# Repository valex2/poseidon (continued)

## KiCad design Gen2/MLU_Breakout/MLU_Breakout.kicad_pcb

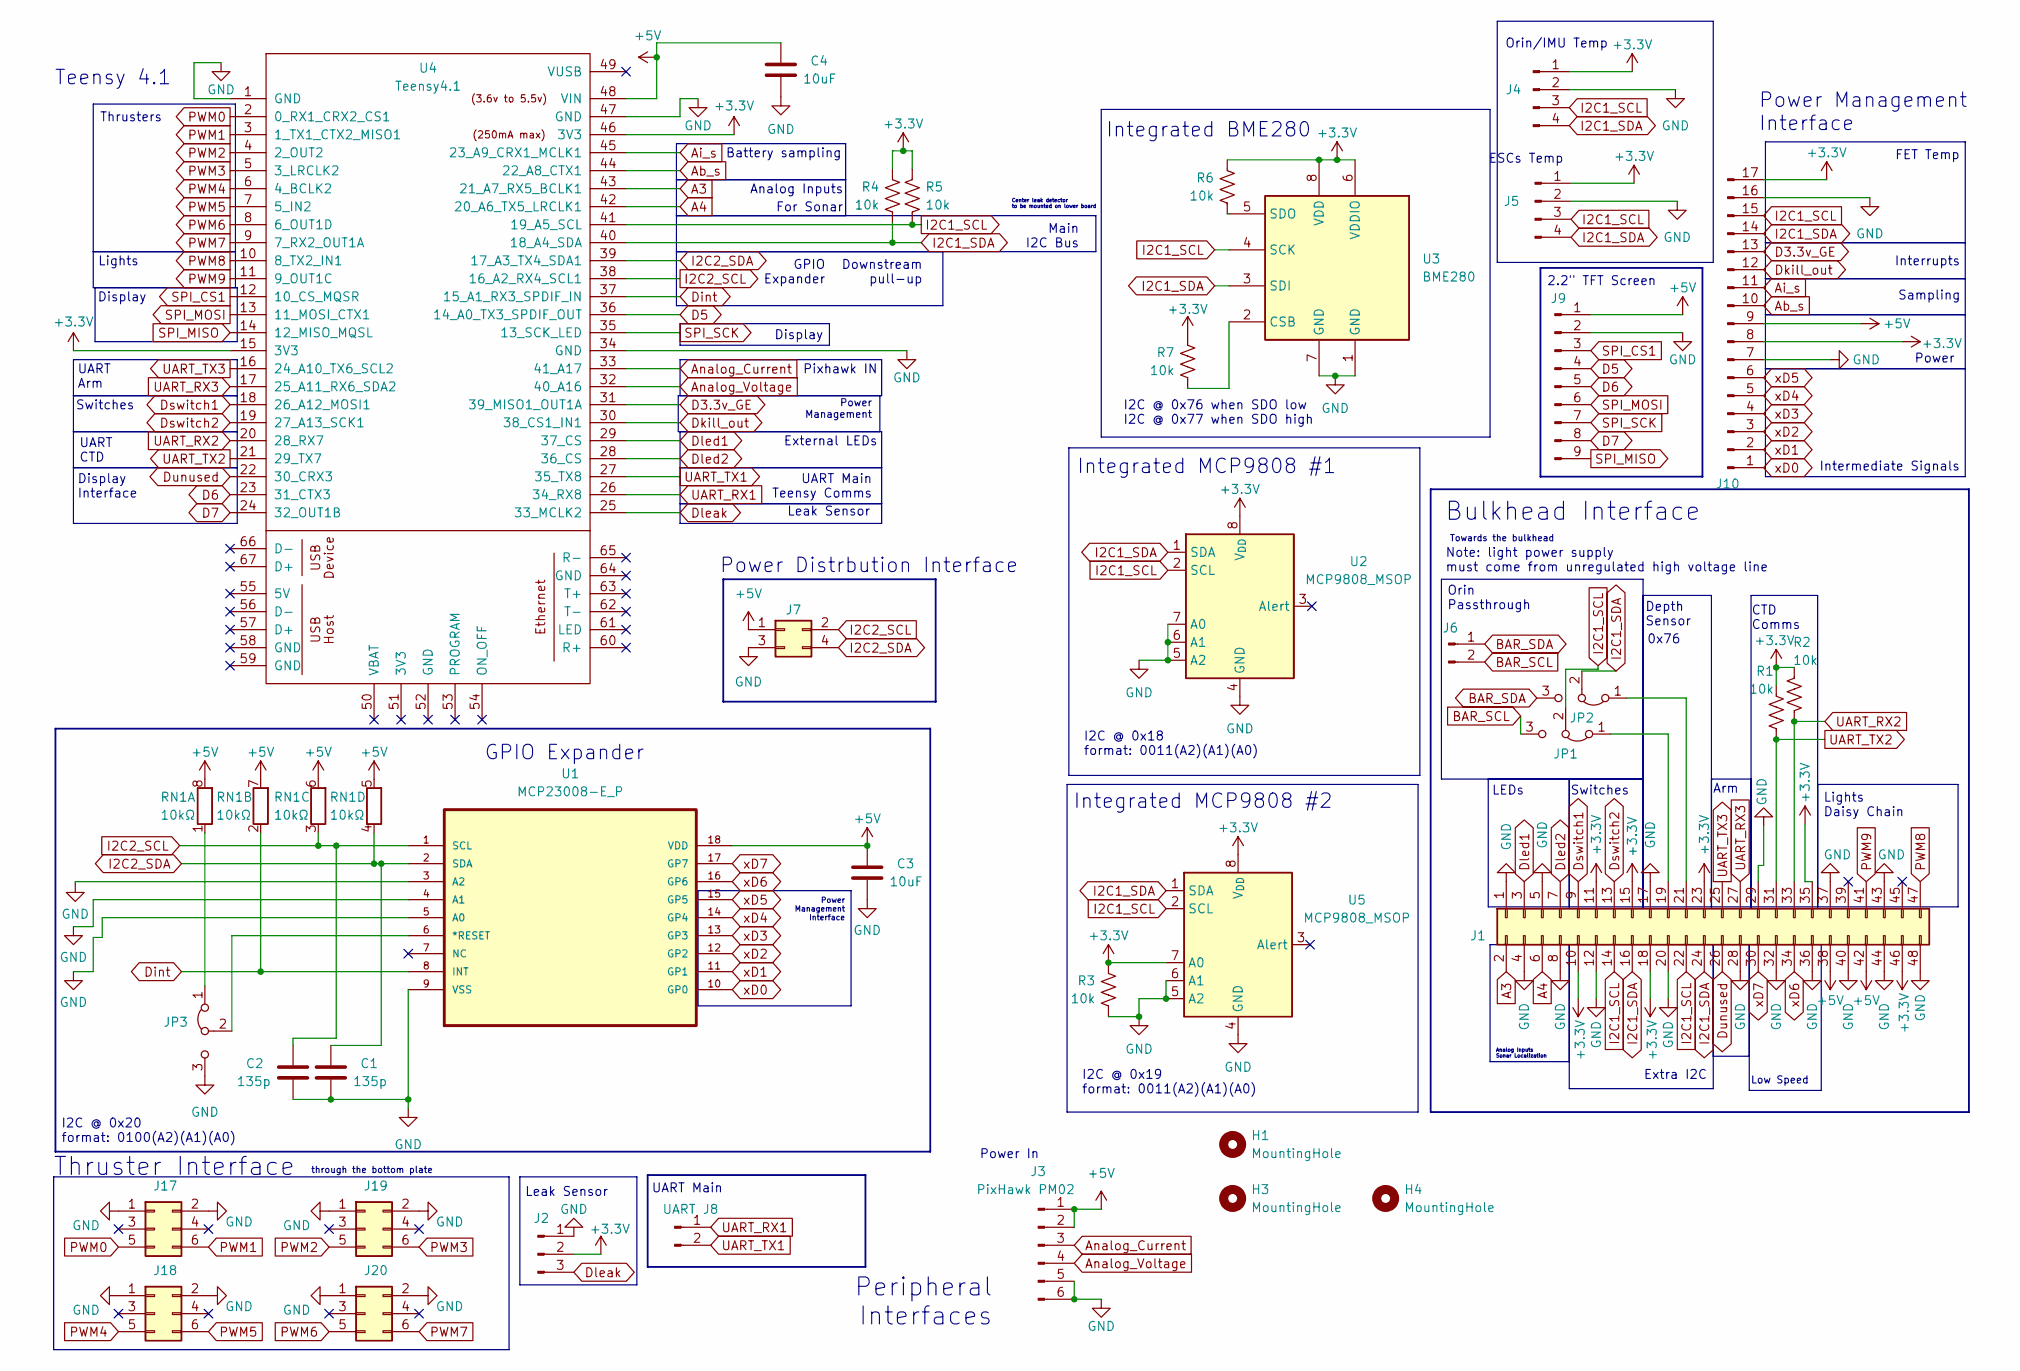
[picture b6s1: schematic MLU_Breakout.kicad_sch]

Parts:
C1, C2: 135p; C_0603_1608Metric_Pad1.08x0.95mm_HandSolder
C3, C4: 10uF; C_0805_2012Metric_Pad1.18x1.45mm_HandSolder
H1, H3, H4: MountingHole; MountingHole_3.2mm_M3
J1: Conn_02x24_Odd_Even; PinSocket_2x24_P2.54mm_Horizontal
J2: Conn_01x03_Pin; PinHeader_1x03_P2.54mm_Vertical
J3: PixHawk PM02; PinSocket_1x06_P2.54mm_Vertical
J4: BUS1; PinSocket_1x04_P2.54mm_Vertical
J5: BUS2; PinSocket_1x04_P2.54mm_Vertical
J6: Conn_01x02_Pin; PinHeader_1x02_P2.54mm_Vertical
J7: Conn_02x02_Odd_Even; PinHeader_2x02_P2.54mm_Vertical
J8: UART; PinSocket_1x02_P2.54mm_Vertical
J9: Conn_01x09_Pin; PinHeader_1x09_P2.54mm_Vertical
J10: Conn_01x17_Pin; PinHeader_1x17_P2.54mm_Horizontal
J17, J18, J19, J20: Conn_02x03_Odd_Even; PinHeader_2x03_P2.54mm_Vertical
JP1, JP2, JP3: Jumper_3_Bridged12; SolderJumper-3_P1.3mm_Bridged2Bar12_RoundedPad1.0x1.5mm
R1, R2, R3, R4, R5, R6, R7: 10k; R_0805_2012Metric_Pad1.20x1.40mm_HandSolder
RN1: 10kΩ; R_Array_Convex_4x0612; Mfr P/N CAY16-103J4LF
U1: MCP23008-E_P; MCP3008; MPN MCP23008-E/P
U2, U5: MCP9808_MSOP; MSOP-8_3x3mm_P0.65mm
U3: BME280
U4: Teensy4.1; Teensy41

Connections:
+3.3V: J1.10, J1.11, J1.15, J1.18, J1.23, J1.35, J1.46, J2.2, J4.1, J5.1, J10.8, J10.17, R1.1, R2.1, R3.1, R4.1, R5.1, R6.1, R7.1, U2.8 (V_{DD}), U3.6 (VDDIO), U3.8 (VDD), U4.15 (3V3), U4.46 (3V3), U5.7 (A0), U5.8 (V_{DD})
+5V: C3.1, C4.1, J1.38, J1.42, J3.1, J3.2, J7.1, J9.1, J10.9, RN1.5 (R4.2), RN1.6 (R3.2), RN1.7 (R2.2), RN1.8 (R1.2), U1.18 (VDD), U4.48 (VIN)
A3: J1.2, U4.43 (21_A7_RX5_BCLK1)
A4: J1.6, U4.42 (20_A6_TX5_LRCLK1)
Ab_s: J10.10, U4.44 (22_A8_CTX1)
Ai_s: J10.11, U4.45 (23_A9_CRX1_MCLK1)
Analog_Current: J3.3, U4.33 (41_A17)
Analog_Voltage: J3.4, U4.32 (40_A16)
BAR_SCL: J6.2, JP1.3 (B)
BAR_SDA: J6.1, JP2.3 (B)
D3.3v_GE: J10.13, U4.31 (39_MISO1_OUT1A)
D5: J9.4, U4.36 (14_A0_TX3_SPDIF_OUT)
D6: J9.5, U4.23 (31_CTX3)
D7: J9.8, U4.24 (32_OUT1B)
Dint: RN1.2 (R2.1), U1.8 (INT), U4.37 (15_A1_RX3_SPDIF_IN)
Dkill_out: J10.12, U4.30 (38_CS1_IN1)
Dleak: J2.3, U4.25 (33_MCLK2)
Dled1: J1.3, U4.29 (37_CS)
Dled2: J1.7, U4.28 (36_CS)
Dswitch1: J1.9, U4.18 (26_A12_MOSI1)
Dswitch2: J1.13, U4.19 (27_A13_SCK1)
Dunused: J1.26, U4.22 (30_CRX3)
GND: C1.2, C2.2, C3.2, C4.2, J1.1, J1.4, J1.5, J1.8, J1.12, J1.17, J1.20, J1.28, J1.29, J1.32, J1.36, J1.37, J1.40, J1.43, J1.44, J1.48, J2.1, J3.5, J3.6, J4.2, J5.2, J7.3, J9.2, J10.7, J10.16, J17.1, J17.2, J18.1, J18.2, J19.1, J19.2, J20.1, J20.2, JP3.3 (B), R3.2, U1.3 (A2), U1.4 (A1), U1.5 (A0), U1.9 (VSS), U2.4 (GND), U2.5 (A2), U2.6 (A1), U2.7 (A0), U3.1 (GND), U3.7 (GND), U4.1 (GND), U4.34 (GND), U4.47 (GND), U5.4 (GND), U5.5 (A2), U5.6 (A1)
I2C1_SCL: J1.14, J1.22, J4.3, J5.3, J10.15, JP1.2 (C), R5.2, U2.2 (SCL), U3.4 (SCK), U4.41 (19_A5_SCL), U5.2 (SCL)
I2C1_SDA: J1.16, J1.24, J4.4, J5.4, J10.14, JP2.2 (C), R4.2, U2.1 (SDA), U3.3 (SDI), U4.40 (18_A4_SDA), U5.1 (SDA)
I2C2_SCL: C2.1, J7.2, RN1.3 (R3.1), U1.1 (SCL), U4.38 (16_A2_RX4_SCL1)
I2C2_SDA: C1.1, J7.4, RN1.4 (R4.1), U1.2 (SDA), U4.39 (17_A3_TX4_SDA1)
unnamed: J1.19, JP1.1 (A)
unnamed: J1.21, JP2.1 (A)
unnamed: JP3.1 (A), RN1.1 (R1.1)
unnamed: JP3.2 (C), U1.6 (*RESET)
unnamed: R7.2, U3.2 (CSB)
unnamed: R6.2, U3.5 (SDO)
PWM0: J17.5, U4.2 (0_RX1_CRX2_CS1)
PWM1: J17.6, U4.3 (1_TX1_CTX2_MISO1)
PWM2: J19.5, U4.4 (2_OUT2)
PWM3: J19.6, U4.5 (3_LRCLK2)
PWM4: J18.5, U4.6 (4_BCLK2)
PWM5: J18.6, U4.7 (5_IN2)
PWM6: J20.5, U4.8 (6_OUT1D)
PWM7: J20.6, U4.9 (7_RX2_OUT1A)
PWM8: J1.47, U4.10 (8_TX2_IN1)
PWM9: J1.41, U4.11 (9_OUT1C)
SPI_CS1: J9.3, U4.12 (10_CS_MQSR)
SPI_MISO: J9.9, U4.14 (12_MISO_MQSL)
SPI_MOSI: J9.6, U4.13 (11_MOSI_CTX1)
SPI_SCK: J9.7, U4.35 (13_SCK_LED)
UART_RX1: J8.1, U4.26 (34_RX8)
UART_RX2: J1.33, R2.2, U4.20 (28_RX7)
UART_RX3: J1.27, U4.17 (25_A11_RX6_SDA2)
UART_TX1: J8.2, U4.27 (35_TX8)
UART_TX2: J1.31, R1.2, U4.21 (29_TX7)
UART_TX3: J1.25, U4.16 (24_A10_TX6_SCL2)
xD0: J10.1, U1.10 (GP0)
xD1: J10.2, U1.11 (GP1)
xD2: J10.3, U1.12 (GP2)
xD3: J10.4, U1.13 (GP3)
xD4: J10.5, U1.14 (GP4)
xD5: J10.6, U1.15 (GP5)
xD6: J1.34, U1.16 (GP6)
xD7: J1.30, U1.17 (GP7)

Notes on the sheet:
UART Main Teensy Comms
Switches
Display Interface
Power Management Interface
For Sonar
Teensy 4.1
Thrusters
Arm
Center leak detector to be mounted on lower board
ESCs Temp
Intermediate Signals
Battery sampling
Lights
Power Management
Lights Daisy Chain
Peripheral Interfaces
Power Distrbution Interface
Integrated BME280
Display
GPIO Expander
Extra I2C
Power
Note: light power supply must come from unregulated high voltage line
I2C @ 0x76 when SDO low I2C @ 0x77 when SDO high
Bulkhead Interface
Low Speed
Sampling
Leak Sensor
Pixhawk IN
Orin/IMU Temp
External LEDs
I2C @ 0x18 format: 0011(A2)(A1)(A0)
I2C @ 0x19 format: 0011(A2)(A1)(A0)
Power In
Thruster Interface
Analog Inputs Sonar Localization
Interrupts
Downstream pull-up
UART Main
CTD Comms

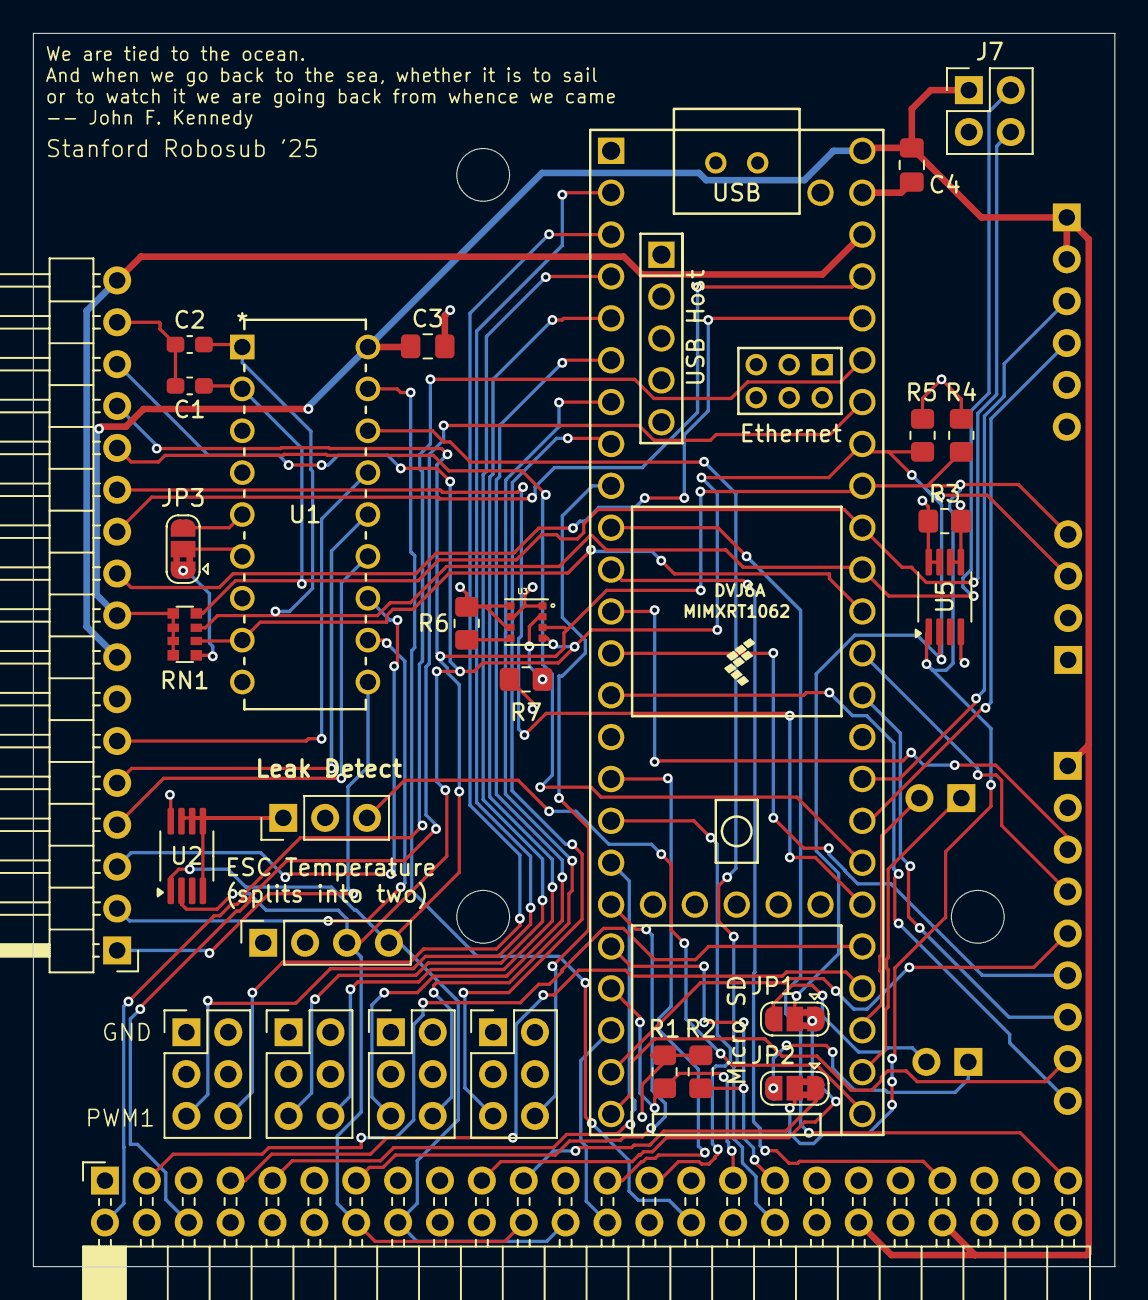
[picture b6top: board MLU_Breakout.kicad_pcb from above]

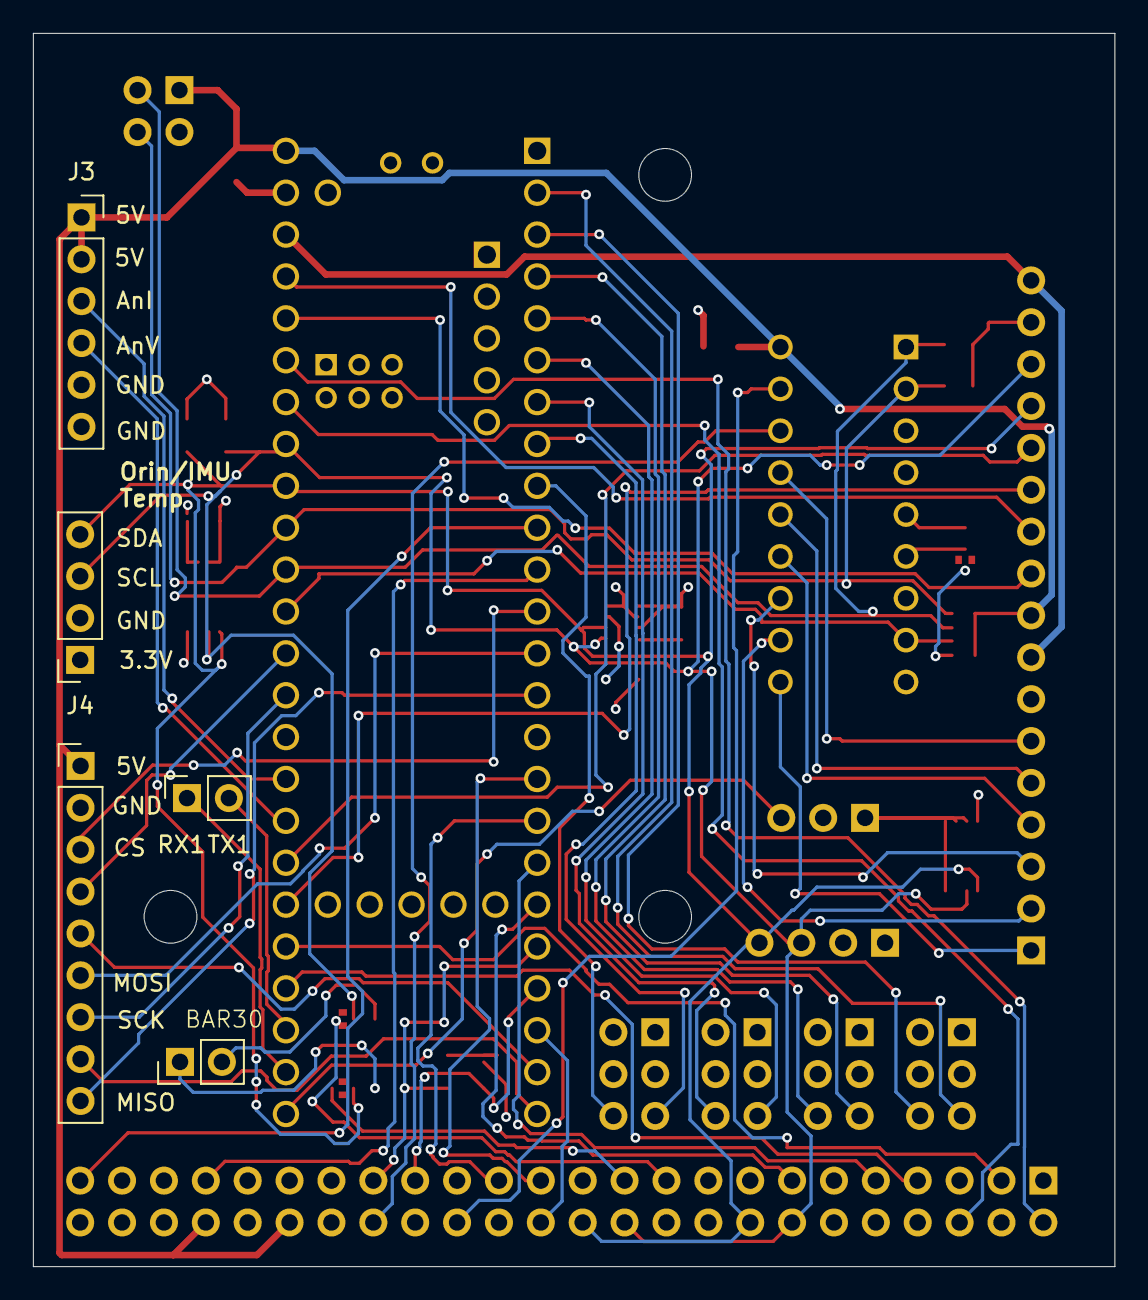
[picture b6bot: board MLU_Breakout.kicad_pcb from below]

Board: 4 copper layers, 65.6 x 74.8 mm, 37 parts (5 on the bottom side), 61 nets.

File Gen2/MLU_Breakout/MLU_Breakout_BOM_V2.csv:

Reference,Value,Qty,DNP,Supplier 1,Supplier 1 P/N,Supplier 1 S/N
"C1,C2",135p,2,,https://www.digikey.com/en/products/detail/murata-electronic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,,490-1427-1-ND
"C3,C4",10uF,2,,https://www.digikey.com/en/products/detail/murata-electronic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,,490-6473-1-ND
"J1,J2,J3,J4,J5,J6,J7,J8,J9,J10,J17,J18,J19,J20,U4",-- mixed values --,15,,,,
"R1,R2,R3,R4,R5,R6,R7",10k,7,,https://www.digikey.com/en/products/detail/panasonic-electro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,,P10KACT-ND
RN1,10kΩ,1,,https://www.digikey.com/en/products/detail/bourns-inc/CAY16-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,,CAY16-103J4LFCT-ND
U1,MCP23008-E_P,1,,https://www.digikey.com/en/products/detail/microchip-technol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,,MCP23008-E/P-ND
"U2,U5",MCP9808_MSOP,2,,https://www.digikey.com/en/products/detail/microchip-technol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,,MCP9808T-E/MSCT-ND
U3,BME280,1,,https://www.digikey.com/en/products/detail/bosch-sensortec/B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,,828-1063-1-ND

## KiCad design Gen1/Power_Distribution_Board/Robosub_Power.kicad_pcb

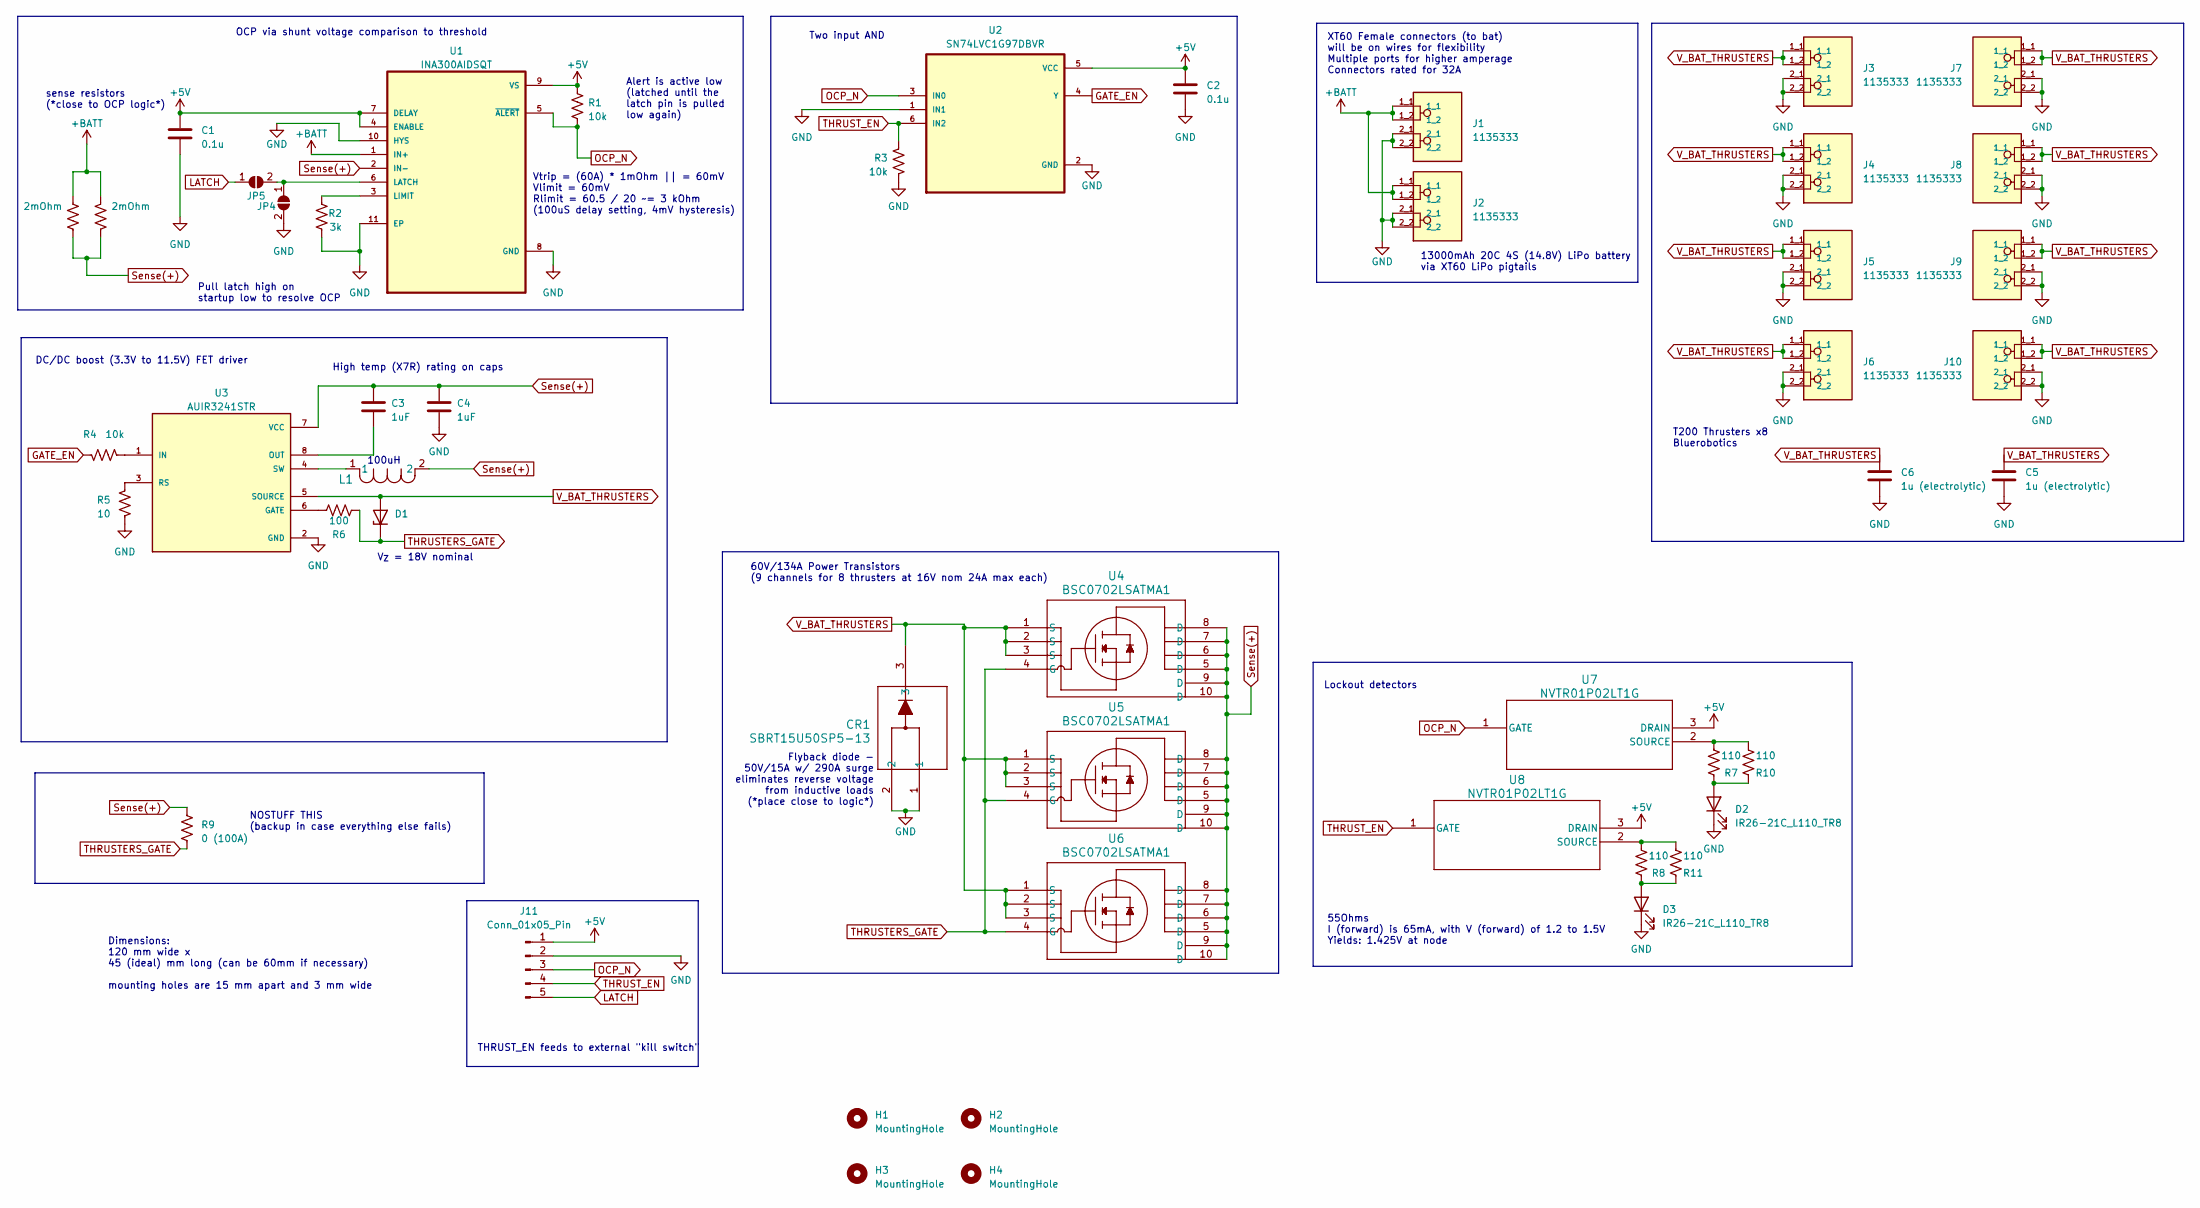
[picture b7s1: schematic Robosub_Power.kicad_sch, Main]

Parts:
C1, C2: 0.1u; C_0805_2012Metric_Pad1.18x1.45mm_HandSolder
C3, C4: 1uF; C_1812_4532Metric_Pad1.57x3.40mm_HandSolder
C5, C6: 1u (electrolytic); UCB1V0R1MCL1GS
CR1: SBRT15U50SP5-13; POWERDI5_DIO
D1: 1SMA5931BT3; D_SMA
D2, D3: IR26-21C_L110_TR8; LED_1206_3216Metric
H1, H2, H3, H4: MountingHole; MountingHole_3.2mm_M3
J1, J2, J3, J4, J5, J6, J7, J8, J9, J10: 1135333; PHOENIX_1135333
J11: Conn_01x05_Pin; PinHeader_1x05_P2.54mm_Vertical
JP4, JP5: SolderJumper_2_Open; SolderJumper-2_P1.3mm_Open_Pad1.0x1.5mm
L1: 74477420; IND_5848-WE-PD2_WRE
R1, R3, R4: 10k; R_0805_2012Metric_Pad1.20x1.40mm_HandSolder
R2: 3k; R_0805_2012Metric_Pad1.20x1.40mm_HandSolder
R5: 10; R_0805_2012Metric_Pad1.20x1.40mm_HandSolder
R6: 100; R_0805_2012Metric_Pad1.20x1.40mm_HandSolder
R7, R8, R10, R11: 110; R_0805_2012Metric_Pad1.20x1.40mm_HandSolder
R9: 0 (100A); R_2512_6332Metric_Pad1.40x3.35mm_HandSolder
U1: INA300AIDSQT; SON40P200X200X80-11N
U2: SN74LVC1G97DBVR; SOT95P280X145-6N
U3: AUIR3241STR; SOIC127P600X175-8N_AUIR3241STR
U4, U5, U6: BSC0702LSATMA1
U7, U8: NVTR01P02LT1G; SOT-23-3_1P4X3P040_ONS
WSLP59312L000FEA_1, WSLP59312L000FEA_2: 2mOhm; RES_WSLP5931_.002OHM_VIS

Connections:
+5V: C1.1, C2.1, J11.1, R1.1, U1.4 (ENABLE), U1.7 (DELAY), U1.9 (VS), U2.5 (VCC), U7.3 (DRAIN), U8.3 (DRAIN)
+BATT: J1.1_1, J1.1_2, J2.1_1, J2.1_2, U1.1 (IN+), WSLP59312L000FEA_1.2, WSLP59312L000FEA_2.2
GATE_EN: R4.1, U2.4 (Y)
GND: C1.2, C2.2, C4.2, C5.2, C6.2, CR1.1, CR1.2, D2.1 (K), D3.1 (K), J1.2_1, J1.2_2, J2.2_1, J2.2_2, J3.2_1, J3.2_2, J4.2_1, J4.2_2, J5.2_1, J5.2_2, J6.2_1, J6.2_2, J7.2_1, J7.2_2, J8.2_1, J8.2_2, J9.2_1, J9.2_2, J10.2_1, J10.2_2, J11.2, JP4.2 (B), R2.2, R3.2, R5.2, U1.8 (GND), U1.10 (HYS), U1.11 (EP), U2.1 (IN1), U2.2 (GND), U3.2 (GND)
LATCH: J11.5, JP5.1 (A)
unnamed: D2.2 (A), R7.1, R10.1
unnamed: D3.2 (A), R8.1, R11.1
unnamed: JP4.1 (A), JP5.2 (B), U1.6 (LATCH)
unnamed: R2.1, U1.3 (LIMIT)
unnamed: R6.1, U3.6 (GATE)
unnamed: R4.2, U3.1 (IN)
unnamed: C3.2, U3.8 (OUT)
unnamed: R5.1, U3.3 (RS)
unnamed: L1.1, U3.4 (SW)
unnamed: R7.2, R10.2, U7.2 (SOURCE)
unnamed: R8.2, R11.2, U8.2 (SOURCE)
OCP_N: J11.3, R1.2, U1.5 (~ALERT), U2.3 (IN0), U7.1 (GATE)
Sense(+): C3.1, C4.1, L1.2, R9.1, U1.2 (IN-), U3.7 (VCC), U4.5 (D), U4.6 (D), U4.7 (D), U4.8 (D), U4.9 (D), U4.10 (D), U5.5 (D), U5.6 (D), U5.7 (D), U5.8 (D), U5.9 (D), U5.10 (D), U6.5 (D), U6.6 (D), U6.7 (D), U6.8 (D), U6.9 (D), U6.10 (D), WSLP59312L000FEA_1.1, WSLP59312L000FEA_2.1
THRUSTERS_GATE: D1.1 (K), R6.2, R9.2, U4.4 (G), U5.4 (G), U6.4 (G)
THRUST_EN: J11.4, R3.1, U2.6 (IN2), U8.1 (GATE)
V_BAT_THRUSTERS: C5.1, C6.1, CR1.3, D1.2 (A), J3.1_1, J3.1_2, J4.1_1, J4.1_2, J5.1_1, J5.1_2, J6.1_1, J6.1_2, J7.1_1, J7.1_2, J8.1_1, J8.1_2, J9.1_1, J9.1_2, J10.1_1, J10.1_2, U3.5 (SOURCE), U4.1 (S), U4.2 (S), U4.3 (S), U5.1 (S), U5.2 (S), U5.3 (S), U6.1 (S), U6.2 (S), U6.3 (S)

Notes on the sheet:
THRUST_EN feeds to external "kill switch"
Two input AND
Lockout detectors
Dimensions: 120 mm wide x 45 (ideal) mm long (can be 60mm if necessary) mounting holes are 15 mm apart and 3 mm wide
High temp (X7R) rating on caps
13000mAh 20C 4S (14.8V) LiPo battery via XT60 LiPo pigtails
Vtrip = (60A) * 1mOhm || = 60mV Vlimit = 60mV Rlimit = 60.5 / 20 ~= 3 kOhm (100uS delay setting, 4mV hysteresis)
Alert is active low (latched until the latch pin is pulled low again)
DC/DC boost (3.3V to 11.5V) FET driver
55Ohms I (forward) is 65mA, with V (forward) of 1.2 to 1.5V Yields: 1.425V at node
XT60 Female connectors (to bat) will be on wires for flexibility Multiple ports for higher amperage Connectors rated for 32A
Flyback diode - 50V/15A w/ 290A surge eliminates reverse voltage from inductive loads (*place close to logic*)
60V/134A Power Transistors (9 channels for 8 thrusters at 16V nom 24A max each)
V_{Z} = 18V nominal
100uH
NOSTUFF THIS (backup in case everything else fails)
T200 Thrusters x8 Bluerobotics
OCP via shunt voltage comparison to threshold
Pull latch high on startup low to resolve OCP
sense resistors (*close to OCP logic*)

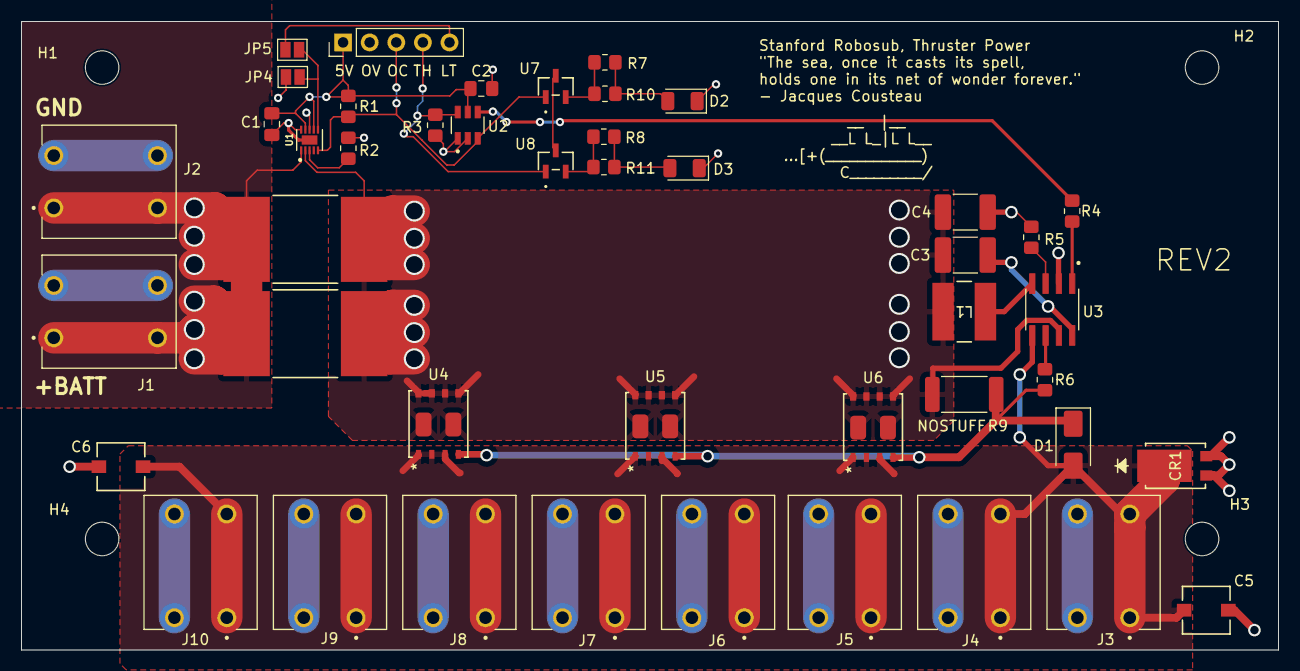
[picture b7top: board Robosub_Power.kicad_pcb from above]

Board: 2 copper layers, 120.0 x 60.0 mm, 49 parts (0 on the bottom side), 21 nets.

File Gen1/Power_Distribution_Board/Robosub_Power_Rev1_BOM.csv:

#,Reference,Qty,Value,Footprint,DNP,Supplier 1,Supplier 1 S/N,MFR,MFR S/N
1,"C1, C2",4,0.1u,Capacitor_SMD:C_0805_2012Metric_Pad1.18x1.45mm_HandSolder,,https://www.digikey.com/en/products/detail/yageo/CC0805KRX7R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,311-1140-1-ND,YAGEO,CC0805KRX7R9BB104
2,"C3, C4",4,1uF,Capacitor_SMD:C_1812_4532Metric_Pad1.57x3.40mm_HandSolder,,https://www.digikey.com/en/products/detail/knowles-syfer/181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,1608-1812Y2000105KSTWS2CT-ND,Knowles Syfer,1812Y2000105KSTWS2
3,"C5, C6",4,1u (electrolytic),Robosub Lib:UCB1V0R1MCL1GS,,https://www.digikey.com/en/products/detail/nichicon/UCB1V0R1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,493-9956-1-ND,Nichicon,UCB1V0R1MCL1GS
4,CR1,2,SBRT15U50SP5-13,SBRT15U50SP5_13:POWERDI5_DIO,,https://www.digikey.com/en/products/detail/diodes-incorporat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,SBRT15U50SP5-13DICT-ND,Diodes Incorporated,SBRT15U50SP5-13
5,D1,2,1SMA5931BT3,Diode_SMD:D_SMA,,https://www.digikey.com/en/products/detail/onsemi/SZ1SMA5931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,SZ1SMA5931BT3GOSCT-ND,onsemi,SZ1SMA5931BT3G
6,"D2, D3",4,IR26-21C_L110_TR8,LED_SMD:LED_1206_3216Metric,,https://www.digikey.com/en/products/detail/everlight-electro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,1080-1357-1-ND,Everlight Electronics Co Ltd,IR26-21C/L110/TR8
7,"H1, H2, H3, H4",8,MountingHole,MountingHole:MountingHole_3.2mm_M3,,,,,
8,"J1, J2, J3, J4, J5, J6, J7, J8, J9, J10",14,1135333,1135333_1:PHOENIX_1135333,,https://www.digikey.com/en/products/detail/phoenix-contact/1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,277-1135333CT-ND,Pheonix Contact,"SPT-THR 2,5/ 2-V-5,0 P20 R32"
9,J14,2,Conn_01x04,Connector_PinHeader_2.54mm:PinHeader_1x04_P2.54mm_Vertical,,,,,
10,"JP4, JP5",4,SolderJumper_2_Open,Jumper:SolderJumper-2_P1.3mm_Open_Pad1.0x1.5mm,,,,,
11,L1,2,74477420,Robosub Lib:IND_5848-WE-PD2_WRE,,https://www.digikey.com/en/products/detail/würth-elektronik/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,732-1278-1-ND,Würth Elektronik,74477420
12,"R1, R3, R4",6,10k,Resistor_SMD:R_0805_2012Metric_Pad1.20x1.40mm_HandSolder,,https://www.digikey.com/en/products/detail/yageo/RC0805FR-07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,311-10.0KCRCT-ND,YAGEO,RC0805FR-0710KL
13,R2,2,3k,Resistor_SMD:R_0805_2012Metric_Pad1.20x1.40mm_HandSolder,,https://www.digikey.com/en/products/detail/te-connectivity-p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,A126368CT-ND,TE Connectivity Passive Product,CRG0805F3K0
14,R5,2,10,Resistor_SMD:R_0805_2012Metric_Pad1.20x1.40mm_HandSolder,,https://www.digikey.com/en/products/detail/yageo/RC0805FR-07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,311-10.0CRCT-ND,YAGEO,RC0805FR-0710RL
15,"R6, R7, R8",6,100,Resistor_SMD:R_0805_2012Metric_Pad1.20x1.40mm_HandSolder,,https://www.digikey.com/en/products/detail/yageo/RC0805FR-07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,311-100CRCT-ND,YAGEO,RC0805FR-07100RL
16,R9,2,0 (100A),Resistor_SMD:R_2512_6332Metric_Pad1.40x3.35mm_HandSolder,,https://www.digikey.com/en/products/detail/bourns-inc./CSS2H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,118-CSS2H-2512C-000ECT-ND,Bourns Inc.,CSS2H-2512C-000E
17,U1,2,INA300AIDSQT,Robosub Lib:SON40P200X200X80-11N,,https://www.digikey.com/en/products/detail/texas-instruments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,296-37474-1-ND,Texas Instruments,INA300AIDSQT
18,U2,2,SN74LVC1G97DBVR,Robosub Lib:SOT95P280X145-6N,,https://www.digikey.com/en/products/detail/texas-instruments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,296-15581-1-ND,Texas Instruments,SN74LVC1G97DBVR
19,U3,2,AUIR3241STR,Robosub Lib:SOIC127P600X175-8N_AUIR3241STR,,https://www.digikey.com/en/products/detail/infineon-technolo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,AUIR3241SCT-ND,Infineon Technologies,AUIR3241STR
20,"U4, U5, U6",6,BSC0702LSATMA1,Robosub Lib:BSC0702LSATMA1,,https://www.digikey.com/en/products/detail/infineon-technolo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,448-BSC0702LSATMA1CT-ND,Infineon Technologies,BSC0702LSATMA1
21,"U7, U8",3,NVTR01P02LT1G,Robosub Lib:SOT-23-3_1P4X3P040_ONS,,https://www.digikey.com/en/products/detail/onsemi/NVTR01P02L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,NVTR01P02LT1GOSCT-ND,onsemi,NVTR01P02LT1G
22,"WSLP59312L000FEA_1, WSLP59312L000FEA_2",4,2mOhm,WSLP59312L000FEA:RES_WSLP5931_.002OHM_VIS,,https://www.digikey.com/en/products/detail/vishay-dale/WSLP5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,541-10013-1-ND,Vishay Dale,WSLP59312L000FEA
23,Hall effect,1,,,,https://www.digikey.com/en/products/detail/littelfuse-inc/55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,55140-3H-02-A-ND,Littelfuse Inc.,55140-3H-02-A
24,Magnet,1,,,,https://www.digikey.com/en/products/detail/littelfuse-inc/H-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,F12127-ND,Littelfuse Inc.,H-58-MAGNET

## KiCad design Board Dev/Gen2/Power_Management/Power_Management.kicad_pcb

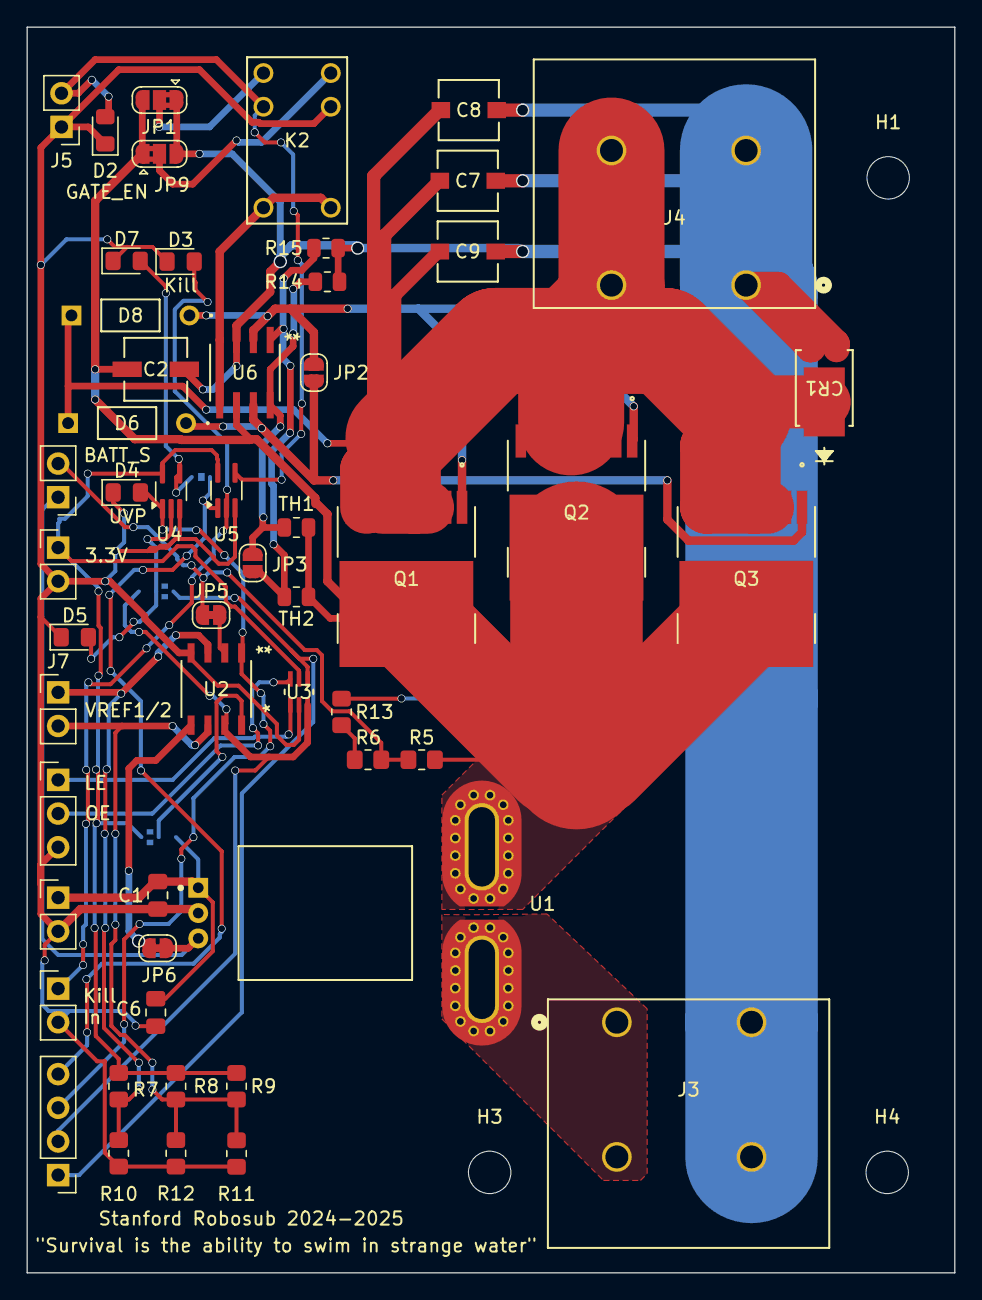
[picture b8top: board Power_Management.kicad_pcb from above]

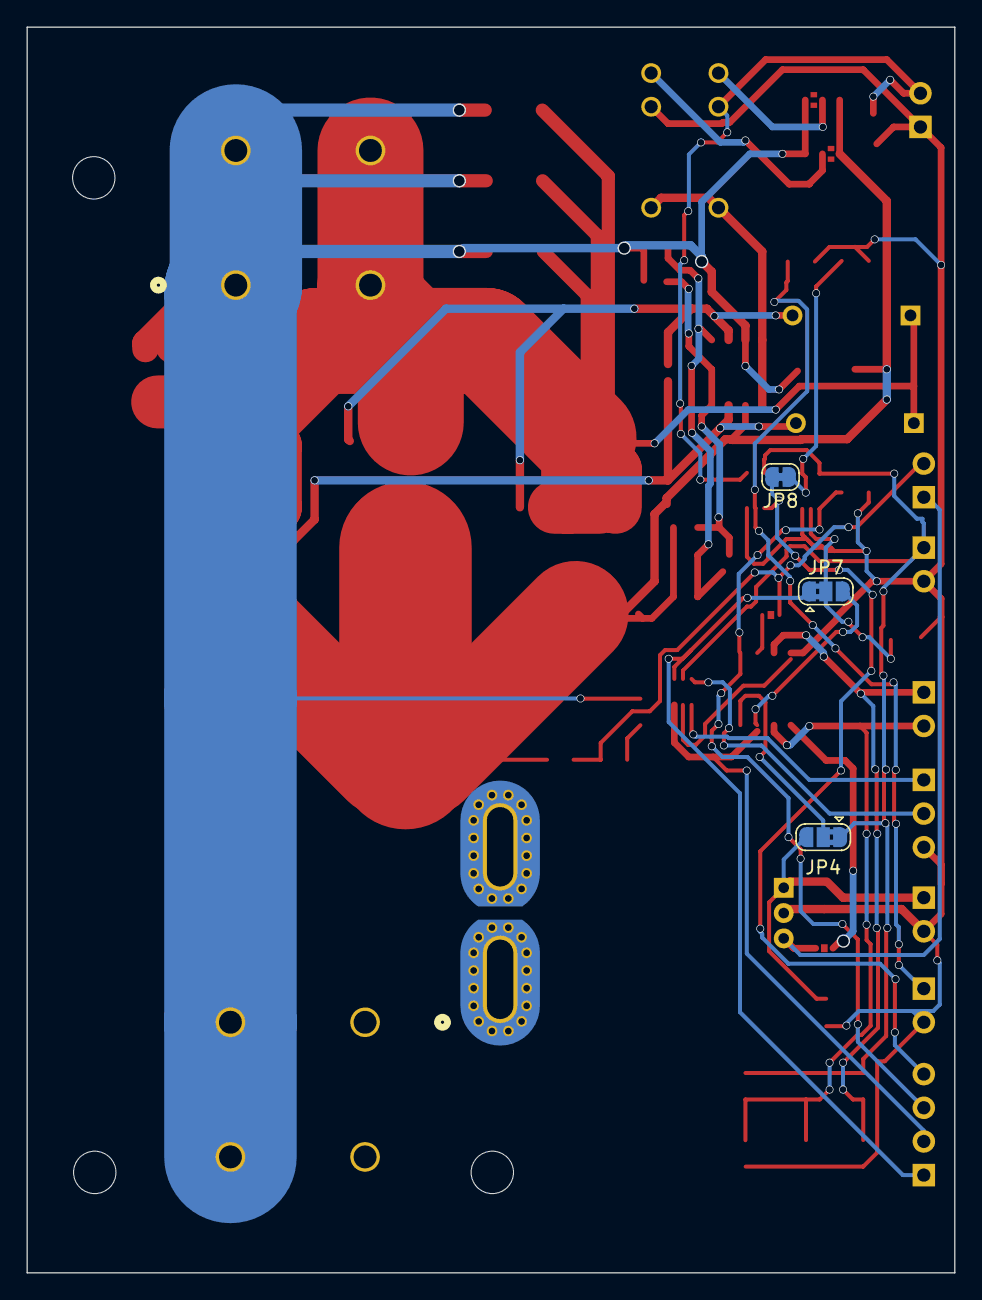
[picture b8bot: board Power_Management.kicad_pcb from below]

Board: 2 copper layers, 70.0 x 94.0 mm, 59 parts (3 on the bottom side), 32 nets.

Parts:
C1: 0.1u; C_0805_2012Metric_Pad1.18x1.45mm_HandSolder
C2: 10uF; CAP_EEE-1CA100SR_PAN
C6: 10uF; C_0805_2012Metric_Pad1.18x1.45mm_HandSolder
C7, C8, C9: 1u; U2-D_NCH
CR1: SBRT15U50SP5-13; POWERDI5_DIO
D2, D3, D4, D5, D7: LED; LED_0805_2012Metric_Pad1.15x1.40mm_HandSolder
D6, D8: D_Zener; 1N5242B
H1, H3, H4: MountingHole; MountingHole_3.2mm_M3
J1, J2, J5, J6, J7, J10: Conn_01x02_Pin; PinHeader_1x02_P2.54mm_Vertical
J3, J4: 1986660-2; CONN2_1986660-2_TEC
J8: Conn_01x04_Pin; PinHeader_1x04_P2.54mm_Vertical
J9: Conn_01x03_Pin; PinHeader_1x03_P2.54mm_Vertical
JP1, JP4, JP7, JP9: SolderJumper_3_Bridged12; SolderJumper-3_P1.3mm_Bridged2Bar12_RoundedPad1.0x1.5mm
JP2, JP3: SolderJumper_2_Open; SolderJumper-2_P1.3mm_Open_RoundedPad1.0x1.5mm
JP5, JP6, JP8: SolderJumper_2_Bridged; SolderJumper-2_P1.3mm_Bridged_RoundedPad1.0x1.5mm
K2: G5V-1 DC3; RELAY_G5V-1_OMR
Q1, Q2, Q3: MCTL160N15Y-TP; TOLL-8L_MCC
R5, R6: 100k; R_0805_2012Metric_Pad1.20x1.40mm_HandSolder
R7: 150k; R_0805_2012Metric_Pad1.20x1.40mm_HandSolder
R8, R9, R11, R12: R_0805_2012Metric_Pad1.20x1.40mm_HandSolder
R10: 200k; R_0805_2012Metric_Pad1.20x1.40mm_HandSolder
R13: 500k; R_0805_2012Metric_Pad1.20x1.40mm_HandSolder
R14, R15: 100k; R_0805_2012Metric
TH1, TH2: Thermistor_US; R_0805_2012Metric
U1: ACS758ECB-200U-PFF-T; Allegro_MicroSystems,_LLC-CB-5-PFF-0-0-MFG
U2: LM393DT
U3: SN74LVC1G373DCKR; SN74LVC
U4, U5: 74LVC1G08; SOT-353_SC-70-5_Handsoldering
U6: LTC1255CS8-PBF; LTC1255

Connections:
+3.3V: J6.1, JP4.1 (A), R7.1, R8.1, R9.1, U3.5 (VCC), U4.5 (VCC), U5.5 (VCC)
+5V: C1.2, C6.1, J2.1, JP4.3 (B), U1.1 (VCC)
/Battery_input/+BATT_HALL: J3.1A, J3.1B, U1.4 (IP+)
/Battery_input/-Batt: C2.2, C7.2, C8.2, C9.2, CR1.1, CR1.2, J3.2A, J3.2B, J4.1A, J4.1B, JP1.1 (A), JP9.3 (B), R13.2, R14.1, R15.1, U6.3 (GND)
/FET_control_logic/3.3V_GATE_EN: D2.2 (A), J5.2, K2.2, U5.4
/FET_control_logic/Kill_Switch: D3.2 (A), J10.1, U5.2
/FET_control_logic/OCP_COMP: J8.2, JP7.3 (B), U2.7 (OUT2), U3.3 (D)
/FET_control_logic/OCP_LATCH: J8.1, JP7.1 (A), U3.4 (Q)
/FET_control_logic/UVP_COMP: D4.2 (A), J8.3, U2.1 (OUT1), U4.1
/FETs/+Batt: C2.1, JP1.3 (B), JP9.1 (A), Q1.9 (D), Q2.9 (D), Q3.9 (D), R5.1, TH1.1, TH2.1, U1.5 (IP-), U6.6 (VS)
/FETs/GATE1_DRIVE: D8.1 (K), JP2.1 (A), Q1.1 (G), Q2.1 (G), U6.2 (GATE1)
/FETs/GATE2_DRIVE: D6.1 (K), JP2.2 (B), Q3.1 (G), U6.7 (GATE2)
/FETs/V_THRUST: C7.1, C8.1, C9.1, CR1.3, D6.2 (A), D8.2 (A), J4.2A, J4.2B, Q1.2 (S), Q1.3 (S), Q1.4 (S), Q1.5 (S), Q1.6 (S), Q1.7 (S), Q1.8 (S), Q2.2 (S), Q2.3 (S), Q2.4 (S), Q2.5 (S), Q2.6 (S), Q2.7 (S), Q2.8 (S), Q3.2 (S), Q3.3 (S), Q3.4 (S), Q3.5 (S), Q3.6 (S), Q3.7 (S), Q3.8 (S)
/OCP_UVP_detect/BATT_SAMPLE: J1.2, JP5.1 (A), R5.2, R6.1
/OCP_UVP_detect/ISENSE_ANALOG: J1.1, JP6.2 (B), U1.3 (VIOUT)
/OCP_UVP_detect/LE_Teensy: J9.1, U3.1 (LE)
/OCP_UVP_detect/OE_Teensy: J9.2, U3.6 (*OE)
GATE_DRIVER_EN: K2.5, K2.6, U6.4 (IN1), U6.5 (IN2)
GND: C1.1, C6.2, D2.1 (K), D3.1 (K), D4.1 (K), D5.1 (K), D7.1 (K), J2.2, J5.1, J6.2, J9.3, J10.2, K2.9, R10.2, R11.2, R12.2, U1.2 (GND), U2.4 (VCC-), U3.2 (GND), U4.3 (GND), U5.3 (GND)
unnamed: D5.2 (A), JP7.2 (C), U4.2
unnamed: D7.2 (A), JP8.1 (A), U4.4
unnamed: J8.4, JP8.2 (B), U5.1
unnamed: JP1.2 (C), K2.1
unnamed: JP3.1 (A), R15.2, TH2.2, U6.1 (DS1)
unnamed: JP3.2 (B), R14.2, TH1.2, U6.8 (DS2)
unnamed: JP4.2 (C), U2.8 (VCC+)
unnamed: JP5.2 (B), U2.2 (IN1-)
unnamed: JP6.1 (A), U2.5 (IN2+)
unnamed: JP9.2 (C), K2.10
unnamed: R6.2, R13.1
VREF1: J7.1, R7.2, R10.1, U2.3 (IN1+)
VREF2: J7.2, R8.2, R9.2, R11.1, R12.1, U2.6 (IN2-)

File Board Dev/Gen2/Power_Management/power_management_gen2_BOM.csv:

Reference,Value,Qty,Supplier 1,Supplier 1 S/N,,Qty (excess)
C1,0.1u,1,https://www.digikey.com/en/products/detail/samsung-electro-m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,1276-1003-1-ND,,3
C2,10uF,1,https://www.digikey.com/en/products/detail/panasonic-electro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,PCE3878CT-ND,,3
C6,10uF,1,https://www.digikey.com/en/products/detail/samsung-electro-m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,1276-1096-1-ND,,3
"C7,C8,C9",1u,3,https://www.digikey.com/en/products/detail/nichicon/UCB1V0R1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,493-9956-1-ND,,5
CR1,SBRT15U50SP5-13,1,https://www.digikey.com/en/products/detail/diodes-incorporat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,SBRT15U50SP5-13DICT-ND,,3
"D2,D3,D4,D5,D7",LED,5,https://www.digikey.com/en/products/detail/w%C3%BCrth-elektr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,732-4982-1-ND,,7
"D6,D8",D_Zener,2,https://www.digikey.com/en/products/detail/onsemi/1N5242B/977596,1N5242B-ND,,4
"H1,H3,H4,J1,J2,J5,J6,J7,J8,J9,J10,R8,R9,R11,R12",-- mixed values --,15,,,,17
"J3,J4",1986660-2,2,https://www.digikey.com/en/products/detail/te-connectivity-a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,A107722-ND,,4
K2,G5V-1 DC3,1,https://www.digikey.com/en/products/detail/omron-electronics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,39-G5V-1DC3-ND,,3
"Q1,Q2,Q3",MCTL160N15Y-TP,3,https://www.digikey.com/en/products/detail/micro-commercial-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,353-MCTL160N15Y-TPCT-ND,,5
"R5,R6,R14,R15",100k,4,https://www.digikey.com/en/products/detail/yageo/RC0805FR-07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,311-100KCRCT-ND,,6
R7,150k,1,https://www.digikey.com/en/products/detail/stackpole-electro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,RMCF0805FT150KCT-ND,,3
R10,200k,1,https://www.digikey.com/en/products/detail/stackpole-electro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,RMCF0805FT200KCT-ND,,3
R13,500k,1,https://www.digikey.com/en/products/detail/stackpole-electro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,738-RNCF0805BTE500KCT-ND,,3
"TH1,TH2",Thermistor_US,2,https://www.digikey.com/en/products/detail/yageo/RC0805FR-07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,311-150CRCT-ND,,4
U1,ACS758ECB-200U-PFF-T,1,https://www.digikey.com/en/products/detail/allegro-microsyst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,620-1356-ND,,3
U2,LM393DT,1,https://www.digikey.com/en/products/detail/rohm-semiconducto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,LM393DTCT-ND,,3
U3,SN74LVC1G373DCKR,1,https://www.digikey.com/en/products/detail/texas-instruments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,296-18775-1-ND,,3
"U4,U5",74LVC1G08,2,https://www.digikey.com/en/products/detail/texas-instruments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,296-11602-1-ND,,4
U6,LTC1255CS8-PBF,1,https://www.digikey.com/en/products/detail/analog-devices-in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,LTC1255CS8#PBF-ND,,3
